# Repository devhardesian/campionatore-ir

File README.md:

# Campionatore IR

**Telecomando universale a infrarossi che funziona senza app né cloud.**

Un ESP32-S3 registra il segnale grezzo di qualsiasi telecomando IR e lo ritrasmette con la stessa portante.
I telecomandi si creano e si usano da una web app installabile (PWA) servita direttamente dal dispositivo:
basta un browser sulla rete di casa, oppure sulla rete Wi-Fi che il dispositivo crea da solo.

> *In English: a universal infrared remote built on an ESP32-S3. It captures raw IR signals from any remote,
> measures the carrier frequency and replays them through the RMT peripheral. It is controlled by a PWA served
> by the device itself, with no cloud and no app. The repository contains the firmware, the web app and the
> KiCad project of a 2-layer PCB with production files.*

- **Campionamento RAW**: registra le durate di ogni impulso e misura la portante (38 kHz, 36 kHz per RC5,
  40 kHz per Sony...), quindi funziona anche con protocolli che una libreria non riconosce, condizionatori compresi.
- **Riproduzione in hardware**: la periferica RMT genera impulsi e portante, senza tempi morti dovuti al software.
- **Web app sul dispositivo**: layout pronti per TV e condizionatore, telecomandi personalizzati, backup e ripristino.
- **Nessuna dipendenza esterna**: si collega alla rete di casa oppure crea un proprio Access Point.
- **PCB pronto per la produzione**: due layer, 48,7 × 37,1 mm, alimentazione e programmazione da USB-C.

## Indice

- [La web app](#la-web-app)
- [Hardware](#hardware)
- [Struttura del repository](#struttura-del-repository)
- [Compilazione e caricamento](#compilazione-e-caricamento)
- [Uso](#uso)
- [API REST](#api-rest)
- [Come funziona](#come-funziona)
- [Produzione del PCB](#produzione-del-pcb)
- [Risoluzione dei problemi](#risoluzione-dei-problemi)
- [Licenza](#licenza)

## La web app

Da sinistra: i telecomandi salvati, un telecomando TV, un condizionatore, la registrazione di un tasto,
la creazione di un telecomando e lo stato del dispositivo.

## Hardware

### Prototipo

Il primo circuito è montato su breadboard attorno a una scheda di sviluppo ESP32-S3:

| Funzione | GPIO | Circuito |
| --- | --- | --- |
| Ricezione | **18** | Catodo del fotodiodo + pull-up 10 kΩ verso 3,3 V, anodo a GND |
| Trasmissione | **17** | 1 kΩ → base di un 2N2222A; LED IR + 2 × 10 Ω dal 5 V al collettore |

### PCB

Il PCB, progettato in KiCad 9, riprende gli stessi pin del prototipo:

| Rif. | Componente | Ruolo |
| --- | --- | --- |
| U1 | ESP32-S3-WROOM-1 | Microcontrollore con Wi-Fi e antenna integrata (sporge oltre il bordo, lontano dal rame) |
| J1 | USB-C (USB 2.0) | Alimentazione 5 V e programmazione tramite la USB nativa dell'ESP32-S3 |
| U3 | USBLC6-2SC6 | Protezione ESD sulle linee dati USB |
| U4 | AP2112K-3.3 | Regolatore lineare 5 V → 3,3 V |
| D2 | SFH4346 | LED IR da 3 mm, pilotato da Q1 (BC818) con 470 Ω sulla base (GPIO 17) e 20 Ω in serie al LED |
| D3 | SFH203FA | Fotodiodo IR con filtro per la luce visibile, pull-up 10 kΩ (GPIO 18) |
| JP1 | Ponticello a saldare | Collega IO0 a GND per forzare la modalità di download, se serve |

Lo schema completo è in [`hardware/campionatore-ir-schema.pdf`](hardware/campionatore-ir-schema.pdf).

## Struttura del repository

```
├── firmware/                     progetto PlatformIO
│   ├── platformio.ini
│   ├── include/config.h          Wi-Fi, pin, tempi di campionamento
│   ├── src/
│   │   ├── main.cpp              avvio, web server
│   │   ├── wifi_manager.*        reti Wi-Fi salvate, Access Point, mDNS
│   │   ├── ir_engine.*           task IR: campionamento, trasmissione RMT, salvataggi
│   │   ├── ir_demod.h            demodulatore software (mark/space + misura della portante)
│   │   ├── json_scan.h           lettore JSON in streaming (backup e vecchi database)
│   │   ├── storage.*             metadati in RAM, segnali su LittleFS
│   │   └── web_api.*             API REST e file statici
│   └── data/www/                 web app: index.html, app.js, style.css, sw.js, manifest, icone
├── hardware/                     progetto KiCad 9
│   ├── ESP32custom.kicad_pro / .kicad_sch / .kicad_pcb
│   ├── campionatore-ir-schema.pdf
│   ├── 3d/campionatore-ir.step   modello 3D della scheda montata
│   └── produzione/               Gerber e forature, distinta componenti (BOM), posizioni (CPL)
└── docs/img/                     immagini di questo README
```

## Compilazione e caricamento

Serve [PlatformIO](https://platformio.org/) (estensione di VS Code oppure riga di comando).

**1. Configura la rete (facoltativo).** Le reti Wi-Fi si aggiungono dalla web app (⋮ → *Wi-Fi e Access
Point*) e restano nella NVS dell'ESP32, quindi sopravvivono a `uploadfs` e agli aggiornamenti del firmware. In
`firmware/include/config.h` puoi comunque indicare una rete predefinita, usata insieme a quelle salvate:

```c
#define WIFI_SSID "NomeRete"
#define WIFI_PASSWORD "password"
```

All'avvio il dispositivo si collega alla rete nota con il segnale migliore. Se nessuna risponde crea l'Access
Point **`Campionatore-IR`** e la web app è su **http://192.168.4.1**; finché nessun telefono è collegato all'AP,
ogni minuto riprova le reti note (utile dopo un black-out, quando il router si riaccende dopo l'ESP32). Se la
rete cade per più di 2 minuti torna in Access Point.

La password predefinita dell'Access Point è `irremote123`: **cambiala** dalla web app. Se la dimentichi, tieni
premuto il tasto **BOOT** per 5 secondi: torna quella predefinita e il dispositivo si riavvia.

**2. Controlla la flash.** `platformio.ini` è impostato per moduli da 8 MB; le righe commentate spiegano come
passare a 4 o 16 MB e come attivare la PSRAM.

**3. Carica firmware e web app.**

```bash
cd firmware
pio run -t upload       # firmware
pio run -t uploadfs     # web app nel filesystem LittleFS
pio device monitor      # log: indirizzo IP, segnali acquisiti, invii
```

Sul PCB la porta seriale passa dalla USB nativa: per vedere i log decommenta `-DARDUINO_USB_CDC_ON_BOOT=1`
in `platformio.ini`. Se la scheda non entra da sola in modalità download, chiudi JP1 con una goccia di stagno,
ricollega la USB e riaprilo dopo il caricamento.

**4. Apri la web app** all'indirizzo stampato sul monitor seriale, oppure su `http://campionatore-ir.local`.
Per averla a schermo intero: menu del browser → *Aggiungi a schermata Home*.

> `uploadfs` riscrive tutta la partizione LittleFS, **compresi i telecomandi salvati**. Prima di aggiornare la
> web app esporta un backup (⋮ → *Esporta backup*) e reimportalo dopo (⋮ → *Importa backup*).

## Uso

- **Nuovo telecomando** (pulsante +): scegli un nome e il tipo.
  - **TV**: Power, Input, Mute, volume, canali, frecce e OK, Menu, Home, Indietro, tastierino numerico.
  - **Condizionatore**: modalità (Cool, Heat, Fan, Dry), temperatura (16–30 °C) e ventola. I condizionatori
    inviano tutto lo stato in ogni segnale, quindi ogni combinazione si registra una volta sola.
  - **Personalizzato**: i tasti che vuoi, ognuno con la sua etichetta.
- **Registrare un tasto**: tocca un tasto tratteggiato e punta il telecomando originale verso il fotodiodo,
  a pochi centimetri.
- **Usare un tasto**: un tocco trasmette; volume, canali e frecce si ripetono tenendoli premuti.
- **✎ Modifica**: un tocco registra di nuovo il tasto, × lo elimina, in fondo c'è *Elimina telecomando*.
- **⋮ → Wi-Fi e Access Point**: stato della connessione, reti salvate (fino a 5, il cestino le dimentica),
  *Aggiungi rete* e *Cambia password* dell'Access Point.
  - *Aggiungi rete* elenca le reti visibili (l'ESP32 vede solo quelle a 2,4 GHz); *Altra rete…* serve per le
    reti nascoste. Una rete viene salvata solo se la connessione riesce.
  - Dall'**Access Point** (primo avvio, nuova casa, router cambiato) il dispositivo prova la rete tenendo acceso
    l'AP e mostra il nuovo indirizzo; l'AP si spegne 2 minuti dopo.
  - Da una **rete di casa**, *Connetti* sposta subito il dispositivo sulla nuova rete (se non ci riesce torna su
    quella di prima), mentre *Salva* la memorizza per quando sarà a portata, per esempio prima di un trasloco.

## API REST

La web app usa le stesse API disponibili a qualsiasi client sulla rete. I parametri vanno come form
(`application/x-www-form-urlencoded`) nelle POST e come query string in GET e DELETE. Le risposte sono JSON;
in caso di errore `{"ok": false, "error": "…"}`.

| Metodo | Endpoint | Parametri | Funzione |
| --- | --- | --- | --- |
| GET | `/api/remotes` | `lite=1` facoltativo | Backup completo (metadati + impulsi); con `lite=1` solo i metadati |
| POST | `/api/remotes` | `name`, `type` (`tv` / `ac` / `custom`) | Crea un telecomando |
| POST | `/api/learn` | `remote`, `button`, `label`, `gap` (ms, facoltativo) | Avvia la cattura di un tasto |
| GET | `/api/learn` | | Stato: `waiting`, `capturing`, `done`, `timeout`, `cancelled`, `error` |
| DELETE | `/api/learn` | | Annulla la cattura |
| POST | `/api/send` | `remote`, `button` | Trasmette il segnale |
| DELETE | `/api/delete` | `remote`, `button` facoltativo | Elimina un tasto o l'intero telecomando |
| POST | `/api/import` | corpo = JSON del backup | Ripristina un backup |
| GET | `/api/info` | | Versione, rete, memoria, spazio sulla flash, tasti registrati |
| GET | `/api/wifi` | | Modalità (`sta` / `ap` / `connecting`), reti salvate, stato dell'AP, ultimo tentativo (`attempt`) |
| GET | `/api/wifi/scan` | `refresh=1` facoltativo | Reti visibili; `scanning: true` finché la ricerca è in corso |
| POST | `/api/wifi/connect` | `ssid`, `password` (vuota per reti aperte) | Prova la rete e, se riesce, la salva |
| POST | `/api/wifi/networks` | `ssid`, `password` | Salva una rete senza collegarsi |
| DELETE | `/api/wifi/networks` | `ssid` | Dimentica una rete salvata |
| POST | `/api/wifi/ap` | `password` (8-63 caratteri ASCII) | Cambia la password dell'Access Point |

Un giro completo da terminale: creare un telecomando, registrare il tasto Power e trasmetterlo.

```bash
# crea il telecomando: la risposta è {"ok":true,"remote":{"id":"3fa2c1d0",…}}
curl -X POST http://campionatore-ir.local/api/remotes -d "name=TV Sala&type=tv"

# avvia la cattura, poi premi Power sul telecomando originale entro 15 s
curl -X POST http://campionatore-ir.local/api/learn -d "remote=3fa2c1d0&button=power&label=Power"
curl http://campionatore-ir.local/api/learn          # ripeti finché lo stato è "done"

# trasmetti
curl -X POST http://campionatore-ir.local/api/send -d "remote=3fa2c1d0&button=power"

# elimina il tasto
curl -X DELETE "http://campionatore-ir.local/api/delete?remote=3fa2c1d0&button=power"
```

Collegare il dispositivo a una rete partendo dall'Access Point:

```bash
curl -X POST http://192.168.4.1/api/wifi/connect -d "ssid=Casa&password=segreta123"
curl http://192.168.4.1/api/wifi                     # "attempt": {"state":"ok","ip":"192.168.1.77",…}
```

Le reti salvate e la password dell'AP non fanno parte del backup e le API non restituiscono mai le password.

Backup e ripristino:

```bash
curl http://campionatore-ir.local/api/remotes -o backup.json
curl -X POST http://campionatore-ir.local/api/import -H "Content-Type: application/json" --data-binary @backup.json
```

Il backup viene prodotto e riletto in streaming, quindi la sua dimensione non è limitata dalla RAM:

```json
{"version":2,
 "remotes":[{"id":"3fa2c1d0","name":"TV Sala","type":"tv",
             "buttons":[{"id":"power","label":"Power","freq":38000,"len":67}]}],
 "signals":[{"r":"3fa2c1d0","b":"power","freq":38000,"raw":[4500,4450,560,…]}]}
```

## Come funziona

### Campionamento

Il fotodiodo non demodula il segnale: durante ogni impulso il pin 18 oscilla alla frequenza della portante.
Il firmware:

1. attende il primo fronte di discesa con un interrupt;
2. campiona il pin con `micros()` in un task ad alta priorità sul core 1;
3. unisce gli impulsi di portante distanti meno di 150 µs in un unico *mark* e misura la portante con la moda
   dell'istogramma dei periodi; se la distribuzione è ambigua scarta la misura e usa 38 kHz;
4. chiude il pacchetto dopo 15 ms di silenzio (50 ms per i condizionatori, che spesso inviano più pacchetti);
5. salva le durate in microsecondi: `[mark, space, mark, …, mark]`.

Se il primo fronte arriva prima che la linea sia rimasta libera per un intero intervallo, la cattura viene
scartata: il telecomando era già in trasmissione e il pacchetto sarebbe incompleto.

In trasmissione la periferica **RMT** genera le durate registrate e la portante misurata, con duty cycle del 33%.
Il demodulatore funziona anche con un ricevitore integrato a tre pin (TSOP38238 e simili) sul GPIO 18; in quel
caso si usa la portante predefinita di 38 kHz.

### Memorizzazione

```
/db.json                        metadati: nomi, etichette, portanti, lunghezze
/sig/<telecomando>/<tasto>.bin  impulsi di un singolo segnale (uint16, µs)
```

In RAM restano solo i metadati, poche decine di byte per tasto; gli impulsi stanno sulla flash e si leggono al
momento dell'invio (14–80 ms). Con 133 tasti la RAM occupata è di circa 20 KB, contro i circa 170 KB della prima
versione, che teneva tutto in un unico JSON in memoria. Un database della versione precedente
(`/remotes.json`) viene convertito automaticamente al primo avvio.

Tempi, soglie e limiti sono tutti in `firmware/include/config.h`.

## Produzione del PCB

In `hardware/produzione/`:

- `campionatore-ir-gerber.zip`: Gerber e forature, da caricare così com'è su JLCPCB o servizi simili;
- `campionatore-ir-bom.csv`: distinta componenti raggruppata per valore e footprint;
- `campionatore-ir-cpl.csv`: posizioni e rotazioni dei componenti per il montaggio.

Controlla le rotazioni nell'anteprima del servizio di montaggio: le convenzioni dei footprint cambiano da un
fornitore all'altro. D2 e D3 sono componenti a foro passante.

Un preventivo reale di JLCPCB, con componenti, montaggio, test e spedizione inclusi: **15,41 €** a scheda su 5
pezzi, **3,43 €** a scheda su 600.

I file di produzione si rigenerano dal progetto con `kicad-cli`:

```bash
cd hardware
kicad-cli pcb export gerbers -o gerber/ --layers F.Cu,B.Cu,F.Paste,B.Paste,F.Silkscreen,B.Silkscreen,F.Mask,B.Mask,Edge.Cuts ESP32custom.kicad_pcb
kicad-cli pcb export drill -o gerber/ --format excellon --excellon-separate-th ESP32custom.kicad_pcb
kicad-cli pcb export pos -o campionatore-ir-cpl.csv --format csv --units mm --side both ESP32custom.kicad_pcb
kicad-cli sch export bom -o campionatore-ir-bom.csv ESP32custom.kicad_sch
```

## Risoluzione dei problemi

- **`campionatore-ir.local` non risponde**: i nomi `.local` (mDNS) viaggiano in multicast sul Wi-Fi e qualche
  risposta va persa. Usa l'indirizzo IP (meglio se riservato nel router) oppure il nome che il router registra
  nel proprio DNS, per esempio `http://campionatore-ir.station/`.
- **Il dispositivo non torna sulla rete di casa**: dopo 2 minuti senza rete accende l'Access Point. Collegati a
  `Campionatore-IR` e controlla le reti da ⋮ → *Wi-Fi e Access Point*; il monitor seriale stampa il motivo di
  ogni tentativo fallito (rete non trovata, password errata…).
- **Il segnale non viene ricevuto**: con un fotodiodo e 10 kΩ di pull-up la sensibilità è bassa, quindi il
  telecomando va tenuto a 1–5 cm. Per più portata porta il pull-up a 47–100 kΩ oppure usa un ricevitore TSOP.
- **Un condizionatore non risponde**: registra di nuovo la combinazione tenendo il telecomando fermo e vicino.
  Il monitor seriale stampa le durate acquisite (`[IR] raw: …`), utili per confrontare due catture.
- **Installazione come app**: i browser abilitano Service Worker e installazione solo su HTTPS. Su `http://<ip>`
  la cache funziona comunque grazie agli ETag; su iPhone l'app aggiunta alla Home si apre a schermo intero anche
  via HTTP.

## Licenza

[MIT](LICENSE)

## Test push

Verifica push con account **DeepDruido** — 12/11/2026.

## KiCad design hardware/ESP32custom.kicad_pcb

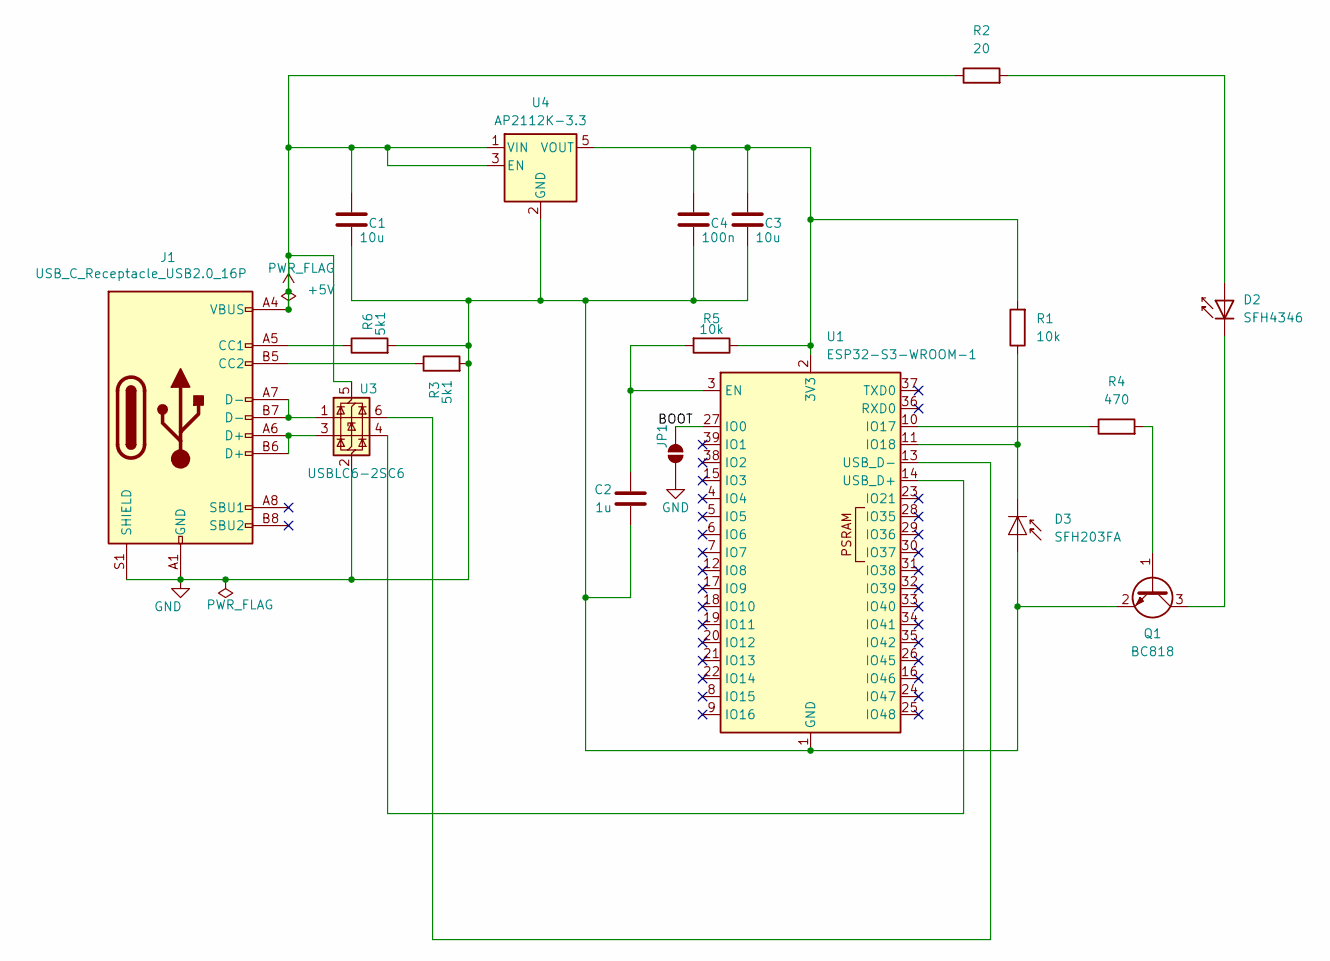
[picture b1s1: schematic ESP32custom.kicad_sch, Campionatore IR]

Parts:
C1, C3: 10u; C_0805_2012Metric
C2: 1u; C_0603_1608Metric
C4: 100n; C_0603_1608Metric
D2: SFH4346; LED_D3.0mm_IRBlack
D3: SFH203FA; LED_D5.0mm_IRGrey
J1: USB_C_Receptacle_USB2.0_16P; USB_C_Receptacle_HRO_TYPE-C-31-M-12
JP1: SolderJumper_2_Open; SolderJumper-2_P1.3mm_Open_RoundedPad1.0x1.5mm
Q1: BC818; SOT-23
R1, R5: 10k; R_0603_1608Metric
R2: 20; R_1206_3216Metric
R3, R6: 5k1; R_0603_1608Metric
R4: 470; R_0603_1608Metric
U1: ESP32-S3-WROOM-1
U3: USBLC6-2SC6; SOT-23-6
U4: AP2112K-3.3; SOT-23-5

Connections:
+5V: C1.1, J1.A4 (VBUS), J1.A9 (VBUS), J1.B4 (VBUS), J1.B9 (VBUS), R2.1, U3.5 (VBUS), U4.1 (VIN), U4.3 (EN)
/BOOT: JP1.1 (A), U1.27 (IO0)
GND: C1.2, C2.2, C3.2, C4.2, D3.2 (A), J1.A1 (GND), J1.A12 (GND), J1.B1 (GND), J1.B12 (GND), J1.S1 (SHIELD), JP1.2 (B), Q1.2 (E), R3.2, R6.2, U1.1 (GND), U1.40 (GND), U1.41 (GND), U3.2 (GND), U4.2 (GND)
unnamed: D2.2 (A), R2.2
unnamed: D2.1 (K), Q1.3 (C)
unnamed: D3.1 (K), R1.1, U1.11 (IO18)
unnamed: J1.A5 (CC1), R6.1
unnamed: J1.B5 (CC2), R3.1
unnamed: J1.A6 (D+), J1.B6 (D+), U3.3 (I/O2)
unnamed: J1.A7 (D-), J1.B7 (D-), U3.1 (I/O1)
unnamed: Q1.1 (B), R4.2
unnamed: C3.1, C4.1, R1.2, R5.1, U1.2 (3V3), U4.5 (VOUT)
unnamed: C2.1, R5.2, U1.3 (EN)
unnamed: R4.1, U1.10 (IO17)
unnamed: U1.14 (USB_D+), U3.4 (I/O2)
unnamed: U1.13 (USB_D-), U3.6 (I/O1)

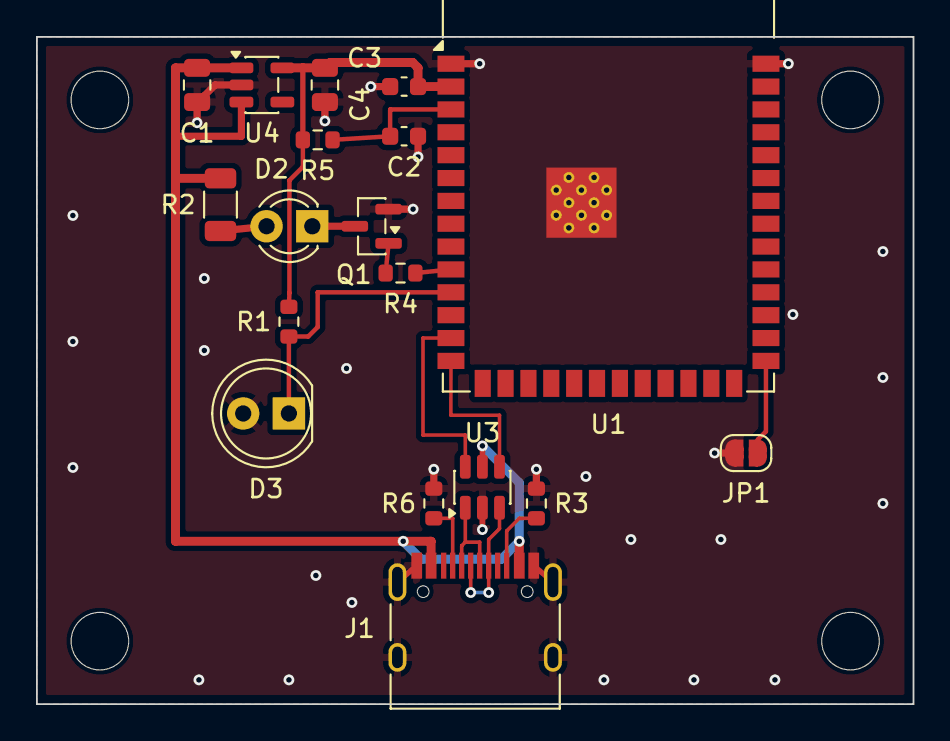
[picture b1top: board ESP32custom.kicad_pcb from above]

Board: 2 copper layers, 48.7 x 37.1 mm, 22 parts (0 on the bottom side), 16 nets.

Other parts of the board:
H1, H2, H3, H4: MountingHole_M3; MountingHole_3.2mm_M3

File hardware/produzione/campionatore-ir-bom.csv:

"Riferimenti","Valore","Footprint","Quantità","Non montare"
"C1,C3","10u","Capacitor_SMD:C_0805_2012Metric","2",""
"C2","1u","Capacitor_SMD:C_0603_1608Metric","1",""
"C4","100n","Capacitor_SMD:C_0603_1608Metric","1",""
"D2","SFH4346","LED_THT:LED_D3.0mm_IRBlack","1",""
"D3","SFH203FA","LED_THT:LED_D5.0mm_IRGrey","1",""
"J1","USB_C_Receptacle_USB2.0_16P","Connector_USB:USB_C_Receptacle_HRO_TYPE-C-31-M-12","1",""
"Q1","BC818","Package_TO_SOT_SMD:SOT-23","1",""
"R1,R5","10k","Resistor_SMD:R_0603_1608Metric","2",""
"R2","20","Resistor_SMD:R_1206_3216Metric","1",""
"R3,R6","5k1","Resistor_SMD:R_0603_1608Metric","2",""
"R4","470","Resistor_SMD:R_0603_1608Metric","1",""
"U1","ESP32-S3-WROOM-1","RF_Module:ESP32-S3-WROOM-1","1",""
"U3","USBLC6-2SC6","Package_TO_SOT_SMD:SOT-23-6","1",""
"U4","AP2112K-3.3","Package_TO_SOT_SMD:SOT-23-5","1",""
